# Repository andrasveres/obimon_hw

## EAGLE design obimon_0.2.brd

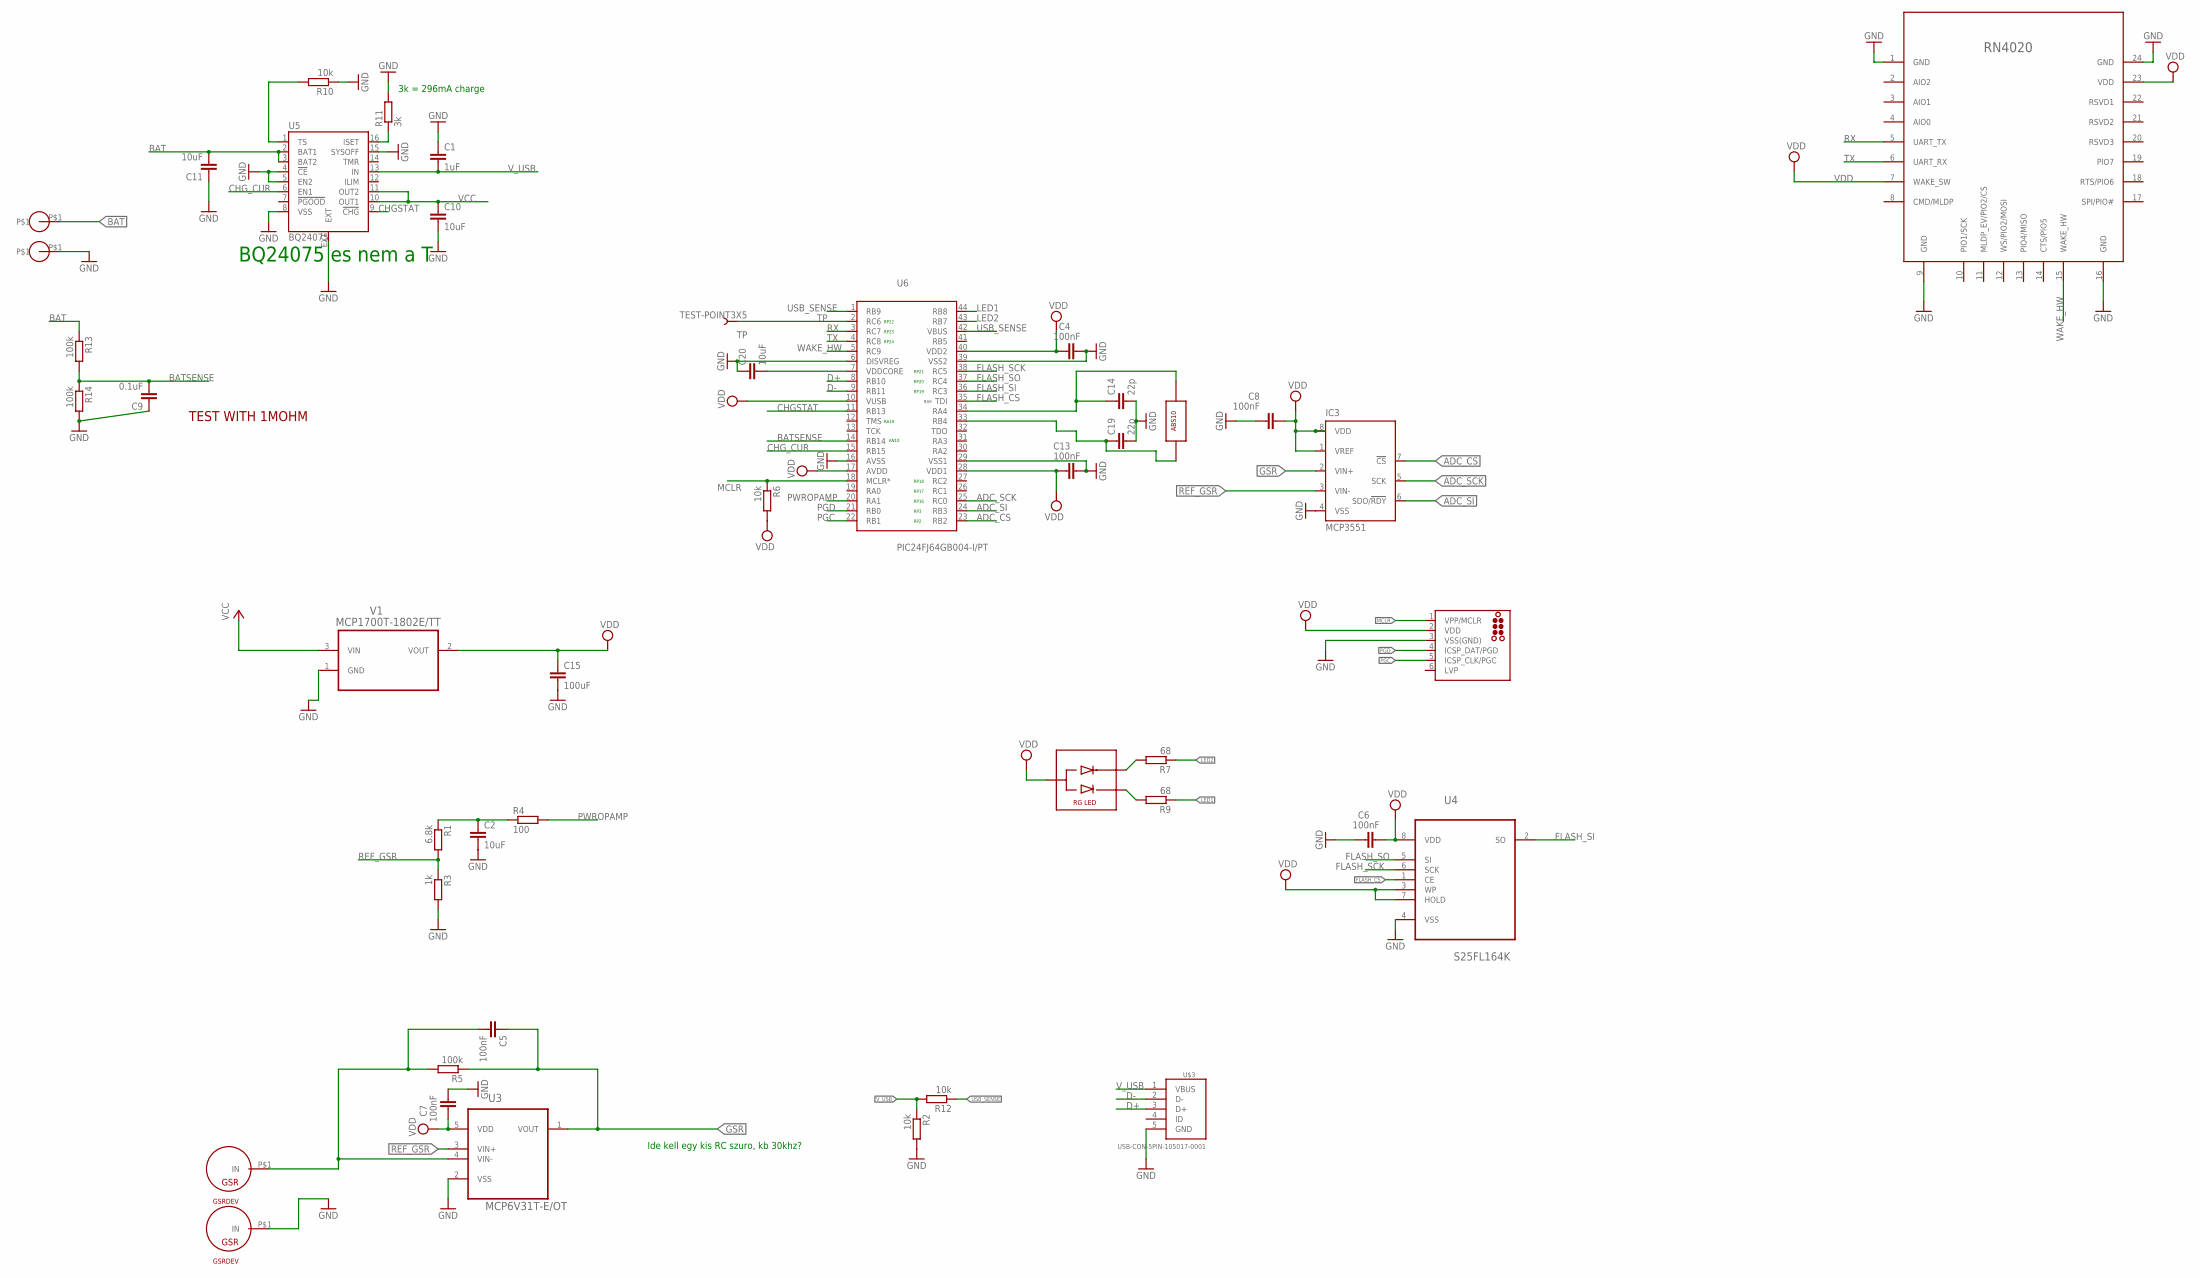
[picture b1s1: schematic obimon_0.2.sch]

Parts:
C1: 1uF; C0805
C2, C10, C11, C20: 10uF; C0805
C4, C5, C6, C7, C8, C13: 100nF; C0805
C9: 0.1uF; C0805
C14, C19: 22p; C0805
C15: 100uF; 1206
IC3: MCP3551; SO-08
J1: TC2030-MCP-NL
LED: LED; REDGREENLED
Q1: ABS10
R1: 6.8k; R0805
R2, R10, R12: 10k; R0805
R3: 1k; R0805
R4: 100; R0805
R5, R13, R14: 100k; R0805
R6: 10k; M0805
R7, R9: 68; R0805
R11: 3k; R0805
TP: TEST-POINT3X5; PAD.03X.05
U3: MCP6V31T-E/OT; SOT95P290X145-5N
U4: S25FL164K; SOIC127P790X216-8N
U5: BQ24075; QFN16_3MM
U6: PIC24FJ64GB004-I/PT; QFP80P1200X1200X120-44N
U$1, U$2: GSRDEV; GSRPAD
U$3: USB-CON-5PIN-105017-0001; USB-MICRO-MOLEX-105017-0001
U$6, U$7: BATPAD
U$8: RN4020
V1: MCP1700T-1802E/TT; SOT95P237X112-3N

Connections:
ADC_CS: IC3.7 (!CS), U6.23 (RB2)
ADC_SCK: IC3.5 (SCK), U6.25 (RC0)
ADC_SI: IC3.6 (SDO/!RDY), U6.24 (RB3)
BAT: C11.2, R13.1, U5.2 (BAT1), U5.3 (BAT2), U$6.P$1
BATSENSE: C9.2, R13.2, R14.1, U6.14 (RB14)
CHGSTAT: U5.9 (!CHG), U6.11 (RB13)
CHG_CUR: U5.6 (EN1), U6.15 (RB15)
D+: U6.8 (RB10), U$3.3 (D+)
D-: U6.9 (RB11), U$3.2 (D-)
FLASH_CS: U4.1 (CE), U6.35 (TDI)
FLASH_SCK: U4.6 (SCK), U6.38 (RC5)
FLASH_SI: U4.2 (SO), U6.36 (RC3)
FLASH_SO: U4.5 (SI), U6.37 (RC4)
GND: C1.1, C2.2, C4.2, C6.1, C7.2, C8.1, C9.1, C10.2, C11.1, C13.2, C14.2, C15.2, C19.2, C20.1, IC3.4 (VSS), J1.3 (VSS(GND)), R2.2, R3.2, R10.1, R11.2, R14.2, U3.2 (VSS), U4.4 (VSS), U5.4 (!CE), U5.5 (EN2), U5.8 (VSS), U5.15 (SYSOFF), U5.EXT, U6.6 (DISVREG), U6.16 (AVSS), U6.29 (VSS1), U6.39 (VSS2), U$2.P$1, U$3.5 (GND), U$7.P$1, U$8.1 (GND), U$8.9 (GND), U$8.16 (GND), U$8.24 (GND), V1.1 (GND)
GSR: C5.1, IC3.2 (VIN+), R5.1, U3.1 (VOUT)
LED1: R9.1, U6.44 (RB8)
LED2: R7.1, U6.43 (RB7)
MCLR: J1.1 (VPP/MCLR), R6.1, U6.18 (MCLR*)
unnamed: R10.2, U5.1 (TS)
unnamed: LED.P$3, R7.2
unnamed: LED.P$1, R9.2
unnamed: R11.1, U5.16 (ISET)
unnamed: C19.1, Q1.P$1, U6.33 (RB4)
unnamed: C2.1, R1.1, R4.1
unnamed: C5.2, R5.2, U3.4 (VIN-), U$1.P$1
unnamed: C14.1, Q1.P$2, U6.34 (RA4)
unnamed: C20.2, U6.7 (VDDCORE)
PGC: J1.5 (ICSP_CLK/PGC), U6.22 (RB1)
PGD: J1.4 (ICSP_DAT/PGD), U6.21 (RB0)
PWROPAMP: R4.2, U6.20 (RA1)
REF_GSR: IC3.3 (VIN-), R1.2, R3.1, U3.3 (VIN+)
RX: U6.3 (RC7), U$8.5 (UART_TX)
TP: TP.P$1, U6.2 (RC6)
TX: U6.4 (RC8), U$8.6 (UART_RX)
USB_SENSE: R12.1, U6.1 (RB9), U6.42 (VBUS)
VCC: C10.1, U5.10 (OUT1), U5.11 (OUT2), V1.3 (VIN)
VDD: C4.1, C6.2, C7.1, C8.2, C13.1, C15.1, IC3.1 (VREF), IC3.8 (VDD), J1.2 (VDD), LED.P$2, R6.2, U3.5 (VDD), U4.3 (WP), U4.7 (HOLD), U4.8 (VDD), U6.10 (VUSB), U6.17 (AVDD), U6.28 (VDD1), U6.40 (VDD2), U$8.7 (WAKE_SW), U$8.23 (VDD), V1.2 (VOUT)
V_USB: C1.2, R2.1, R12.2, U5.13 (IN), U$3.1 (VBUS)
WAKE_HW: U6.5 (RC9), U$8.15 (WAKE_HW)

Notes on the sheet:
RP23
RP16
RP17
RP18
RP24
RP22
TEST WITH 1MOHM
Ide kell egy kis RC szuro, kb 30khz?
3k = 296mA charge
RP2
RP3
RA9
RP19
RP20
RP21
RA10
AN10
BQ24075 es nem a T

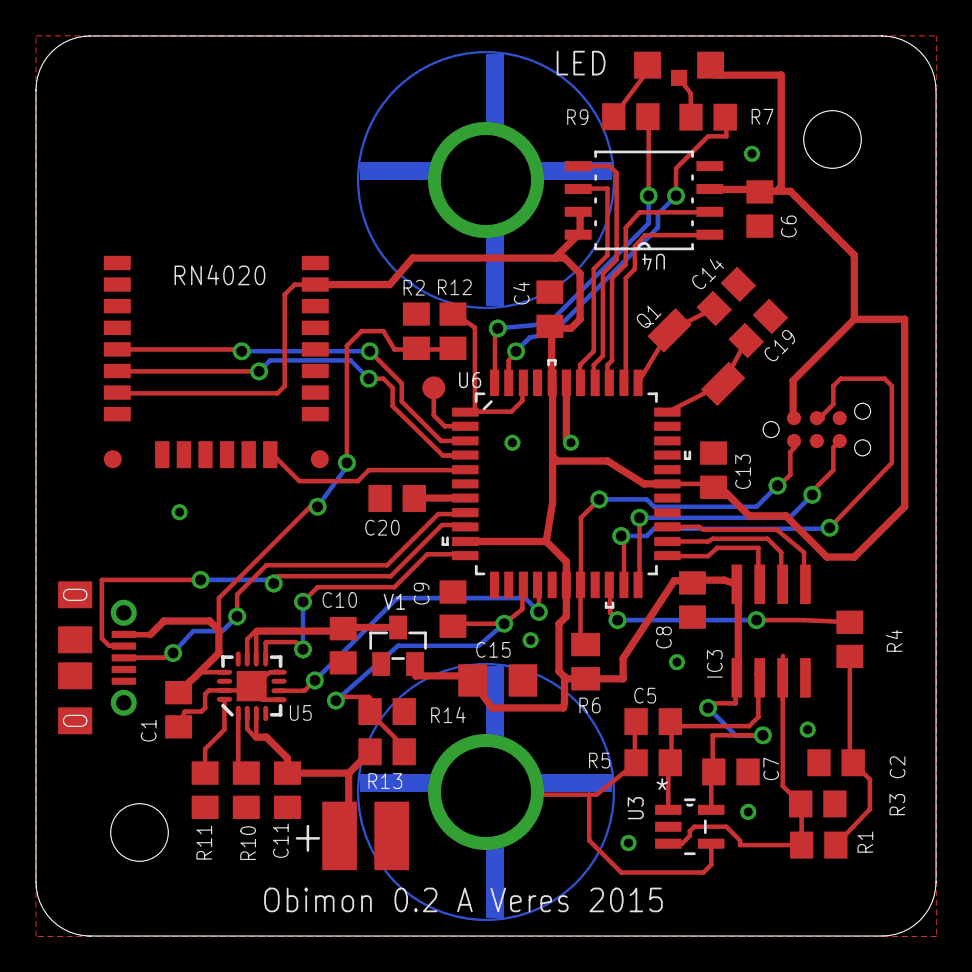
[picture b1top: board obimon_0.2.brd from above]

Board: 2 copper layers, 50.0 x 50.0 mm, 44 parts (0 on the bottom side), 39 nets.

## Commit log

2017-10-22 First

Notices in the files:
parts and their libraries:
SparkFun-Capacitors: Licensing: CC v3.0 Share-Alike You are welcome to use this library for commercial purposes.
tag-connect: ©2009 ROFA.cz - modified and updated by Robert Darlington ‹rdarlington@gmail.com›
